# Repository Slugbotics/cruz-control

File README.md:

# f1tenth-2023

## CatCNN:
This requires miniconda for ease-of-use.
Note: Before running, change the `CatNN.yml` prefix field to match your conda environment location.
Follow this guide to copy the conda packages to your local environment: https://stackoverflow.com/questions/76864397/how-to-replicate-a-conda-environment#76867905

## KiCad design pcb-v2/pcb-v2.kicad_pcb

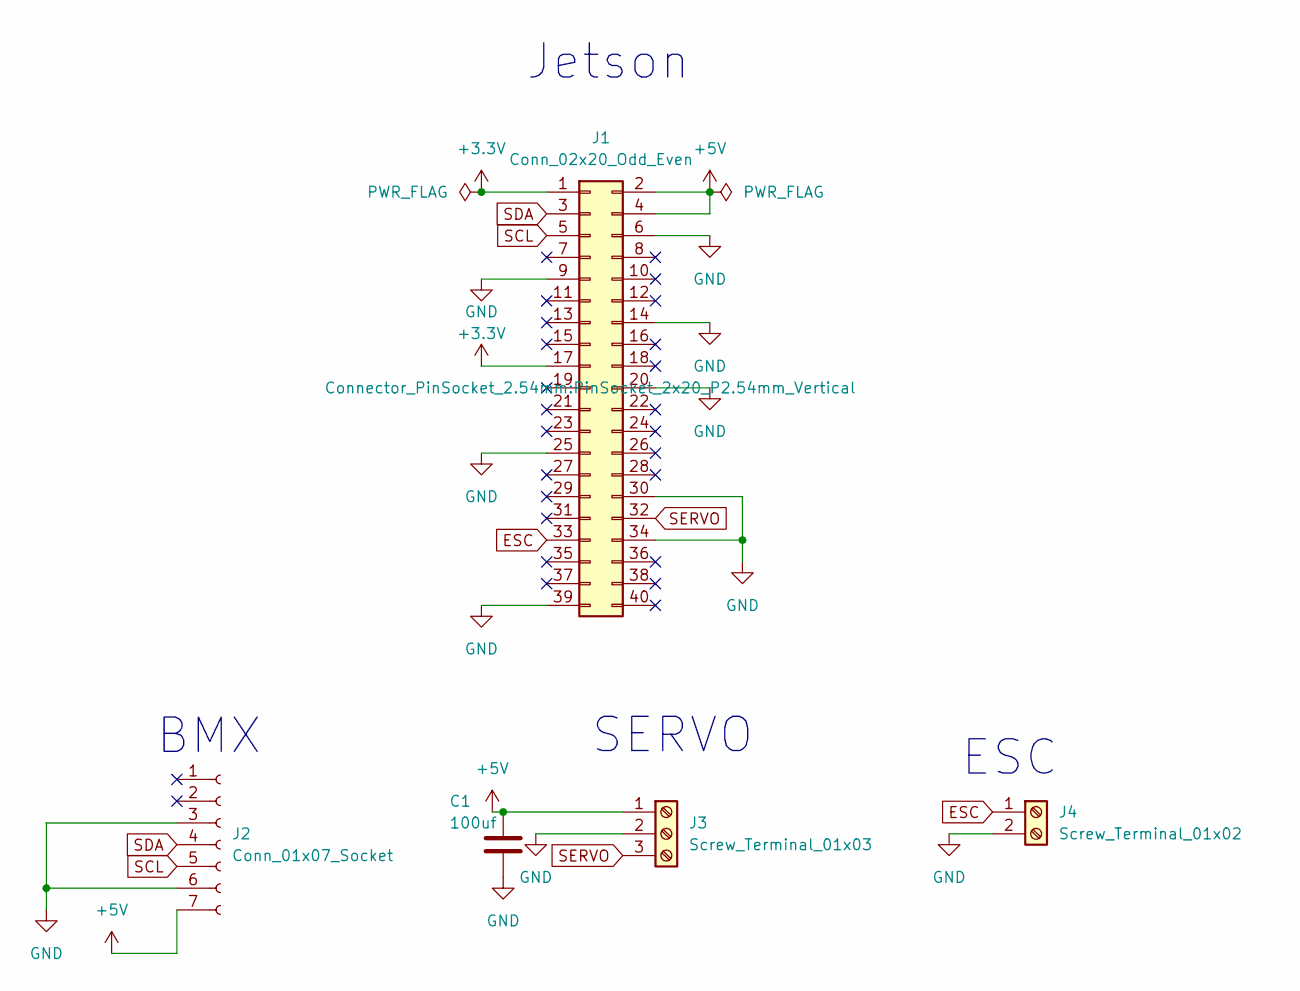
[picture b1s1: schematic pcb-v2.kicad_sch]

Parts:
C1: 100uf; CP_Radial_Tantal_D10.5mm_P5.00mm
J1: Conn_02x20_Odd_Even; PinSocket_2x20_P2.54mm_Vertical
J2: Conn_01x07_Socket; PinHeader_1x07_P2.54mm_Vertical
J3: Screw_Terminal_01x03; PinHeader_1x03_P2.54mm_Horizontal
J4: Screw_Terminal_01x02; PinHeader_1x02_P2.54mm_Horizontal

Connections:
+3.3V: J1.1, J1.17
+5V: C1.1, J1.2, J1.4, J2.7, J3.1
ESC: J1.33, J4.1
GND: C1.2, J1.6, J1.9, J1.14, J1.20, J1.25, J1.30, J1.34, J1.39, J2.3, J2.6, J3.2, J4.2
SCL: J1.5, J2.5
SDA: J1.3, J2.4
SERVO: J1.32, J3.3

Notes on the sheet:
BMX
SERVO
ESC
Jetson

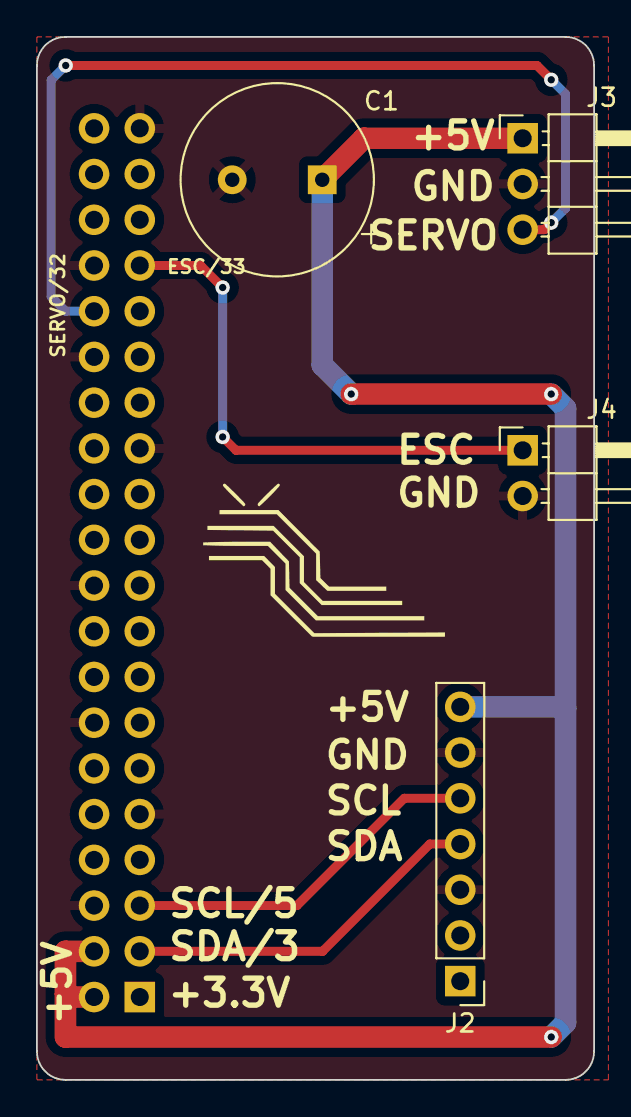
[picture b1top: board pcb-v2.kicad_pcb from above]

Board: 2 copper layers, 31.0 x 57.9 mm, 5 parts (1 on the bottom side), 7 nets.

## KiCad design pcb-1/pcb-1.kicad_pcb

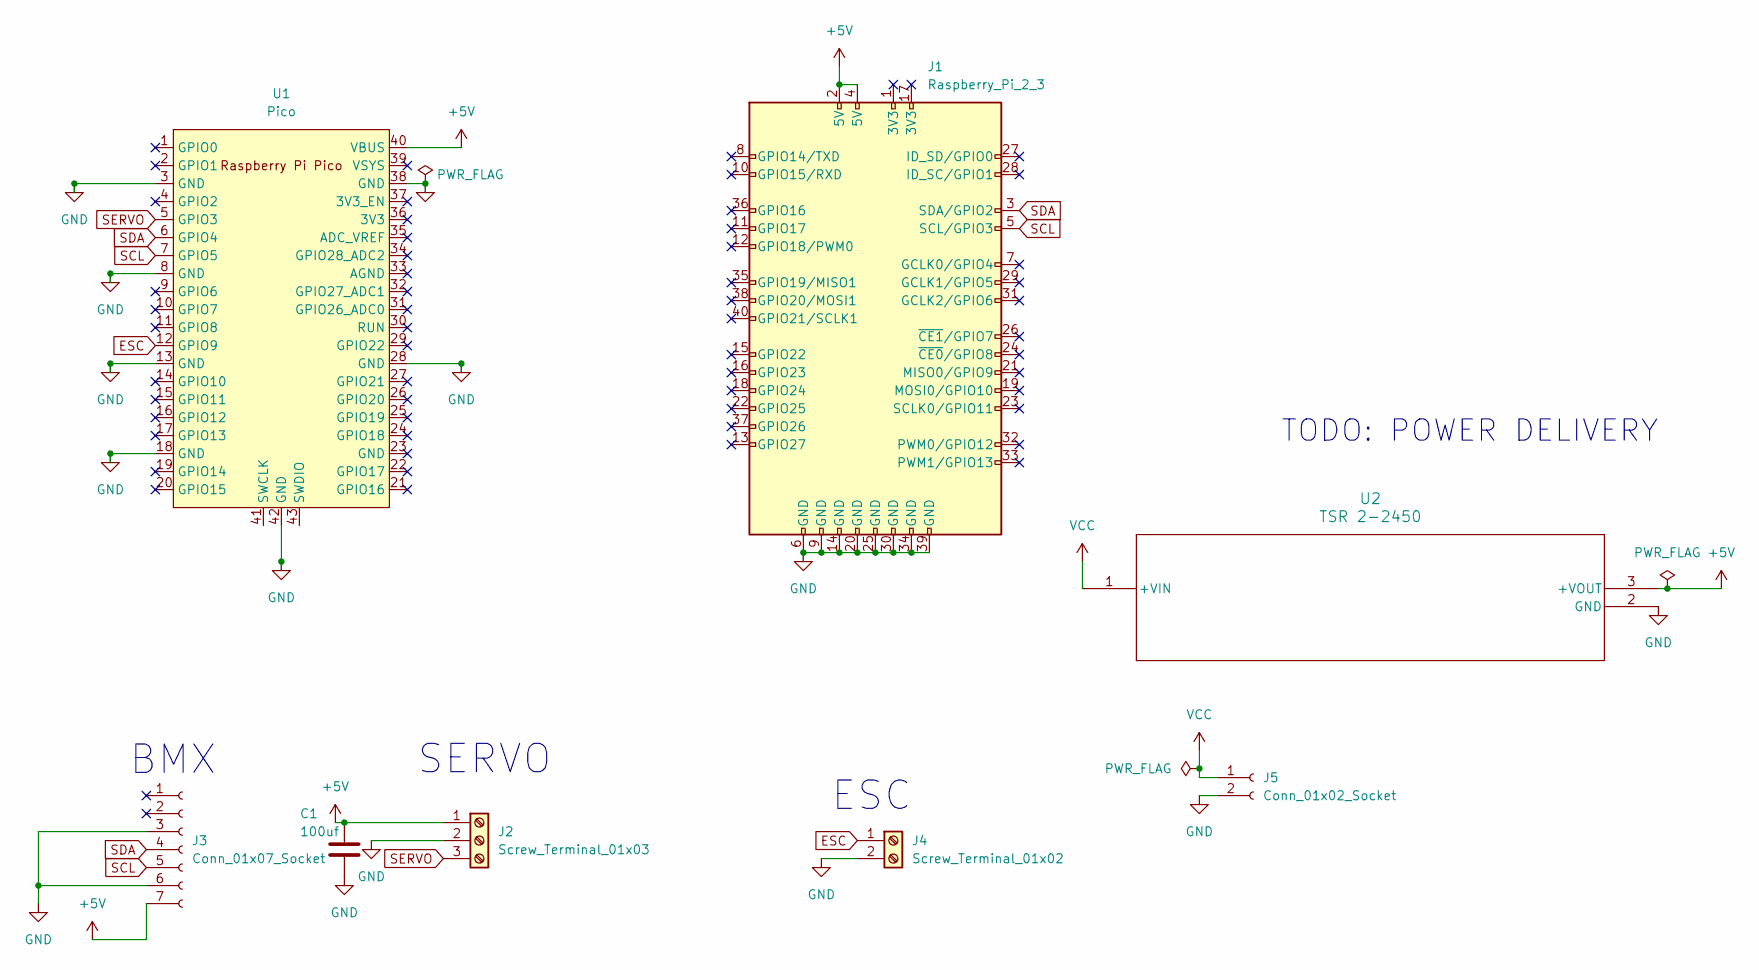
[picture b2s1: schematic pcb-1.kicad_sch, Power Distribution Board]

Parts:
C1: 100uf; CP_Radial_Tantal_D10.5mm_P5.00mm
J1: Raspberry_Pi_2_3; raspberrypi_2_3
J2: Screw_Terminal_01x03; CONN_1935174_PXC
J3: Conn_01x07_Socket; PinHeader_1x07_P2.54mm_Vertical
J4: Screw_Terminal_01x02; CONN2_710002_WRE
J5: Conn_01x02_Socket; AMASS_XT60-F_1x02_P7.20mm_Vertical
U1: Pico; RPi_Pico_SMD_TH
U2: TSR 2-2450; TSR 2-2450_TRP

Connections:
+5V: C1.1, J1.2 (5V), J1.4 (5V), J2.1, J3.7, U1.40 (VBUS), U2.3 (+VOUT)
ESC: J4.1, U1.12 (GPIO9)
GND: C1.2, J1.6 (GND), J1.9 (GND), J1.14 (GND), J1.20 (GND), J1.25 (GND), J1.30 (GND), J1.34 (GND), J1.39 (GND), J2.2, J3.3, J3.6, J4.2, J5.2, U1.3 (GND), U1.8 (GND), U1.13 (GND), U1.18 (GND), U1.28 (GND), U1.38 (GND), U1.42 (GND), U2.2 (GND)
SCL: J1.5 (SCL/GPIO3), J3.5, U1.7 (GPIO5)
SDA: J1.3 (SDA/GPIO2), J3.4, U1.6 (GPIO4)
SERVO: J2.3, U1.5 (GPIO3)
VCC: J5.1, U2.1 (+VIN)

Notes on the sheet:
TODO: POWER DELIVERY
BMX
ESC
SERVO

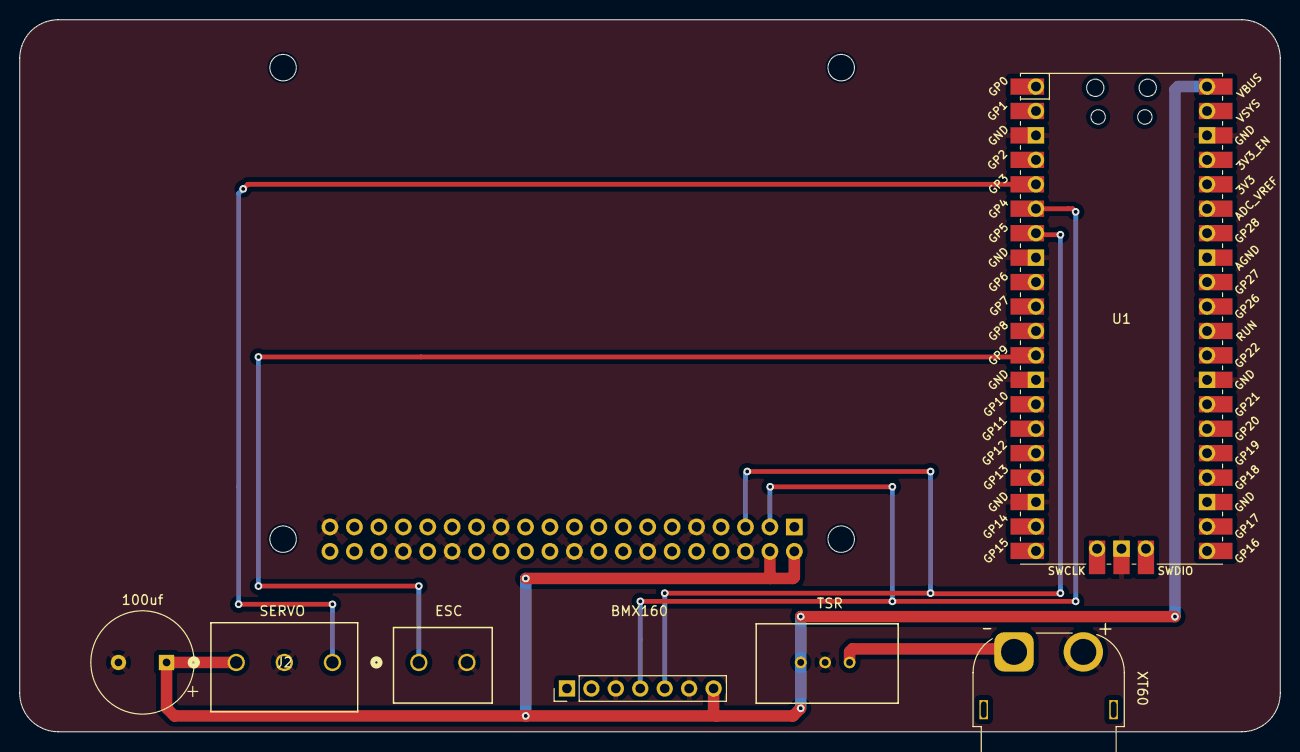
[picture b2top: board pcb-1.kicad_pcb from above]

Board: 2 copper layers, 131.0 x 74.0 mm, 9 parts (0 on the bottom side), 7 nets.

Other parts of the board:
BMX160-Drawing: LOGO

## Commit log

2023-11-22 time-to-collision braking
    Added lab2 automatic braking, read readme
2023-12-01 Added to readme, added lab3ws
2023-12-01 undid changes to main lab3branch
2023-12-01 undid commit to lab2
2023-12-03 added lab2_ws
    added lab2_ws
2024-01-17 Tested arduino servo library
    plan to have -90 to 90 sent from Raspberry Pi, arduino reads from 0 to 180 with 90 being center. use i2c comm with arduino being slave
2024-01-22 picoi2ccms
    added pico i2c comm file
2024-01-23 Added PCB files and Pico code
2024-01-24 Fixed i2c communication & implemented imu for pico
2024-01-24 modified: Pico/Pico.ino
2024-01-24 added camera files to git
2024-01-24 testing files
2024-01-24 finished i2c communication
2024-01-24 servo and esc communication
2024-01-25 Test
2024-01-25 ESC Test
2024-01-25 i2c communication updates
2024-01-26 Updated pico code
    mapped input to value ranges
2024-01-29 intial pcb push
2024-01-29 updated directory naming, completed routing? (still unsure about decoupling cap location)
2024-01-29 pcb rerouted with updated trace widths/dimensions
2024-01-29 removed bad 3v3 net, adjusted dimensions
2024-01-29 flipped pi - consider rerouting bmx160 so it isn't hanging off the board?
2024-01-29 moved trace down a little to avoid thermal relief warning
2024-01-29 added gitignore
2024-01-30 added camera test
2024-01-30 Added code for camera test
2024-01-30 updates to pcb
2024-01-30 deleted lockfile
2024-01-30 refill zones
2024-01-31 added gerber files
2024-02-01 Initial upload of convolutional neural network
2024-02-02 update documentation
2024-02-02 Add package list and retrained model
2024-02-02 push
2024-02-03 Lane Following V1
2024-02-06 Added code to spawn ego vehicle in carla script, must add control features from the lane follow model
2024-02-08 Controller worky
2024-02-08 lane_follow/lane_following.py
2024-02-08 added master.py
2024-02-09 Controller wireless working
2024-02-09 Added code to carla simulation script, but still need to work on image generation/processing
2024-02-10 added bluetooth controller support
    btc support bluetooth controllers, use instead of master.py
2024-02-12 modified: .gitignore modified: Pi/btc.py new file: VisionML/dk_loader.py new file: VisionML/eval.py new file: VisionML/model.py new file: VisionML/model2.py new file: VisionML/train.py new file: Visi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
2024-02-12 removed softmax from model output
2024-02-12 Added title to board
2024-02-13 test commit bluetooth controller
2024-02-13 fixed/cleaned btc.py
    fixed order, added named variables, cleaned up general bugs
2024-02-14 Working bluetooth code
2024-02-14 Merged code to master.py, File name changes
    Renamed files, combined bluetooth controller code together and sensor code to record into csv file
    Added comments to main
    Renamed files
2024-02-14 Working
2024-02-14 added csvfield parameter to csvwriter
    would not compile without having the fieldname parameter
2024-02-14 bugfixes
2024-02-14 modified: VisionML/dk_loader.py modified: VisionML/eval.py modified: VisionML/model2.py modified: VisionML/train2.py
2024-02-15 modified: bluetooth_control.py new file: bt_all.py modified: master.py
2024-02-15 Added
2024-02-15 Adjusted code to generate environment from camera POV, model code is commented out at the moment
2024-02-15 Removed vehicle randomness
2024-02-16 Center Servo
2024-02-16 Added pi code
2024-02-16 Cooked
2024-02-16 Adjusted camera location and car type
2024-02-17 Ignore .avi
2024-02-17 Camera input is working but ValueError occurs when passing input to model
2024-02-18 Added comments and dely to pico code
2024-02-19 cleanup variable names, assignment
    small cleanup to variable names
    (target -> throttle)
    changed how logic was done to determine sign integer
2024-02-19 changed directory saving for train2.py
2024-02-20 Model input is now working
2024-02-20 modified: master.py
2024-02-20 update slave address
2024-02-21 Added Pi control of servos in bluetooth_test.py
    added servo library, clean up code, add comments
2024-02-21 removed extra bluetooth files
2024-02-21 fixed XB_AXIS_MAP
    enum can now be read immediately as .value instead of an enum object with a value and name, use like c++ enums now
2024-02-21 mapping change on steer to percent
    change from angle to percent, as the servo already gives its max range as -1, 1
2024-02-22 init pcb-v2
2024-02-22 pcb-v2 r1
2024-02-22 pcb-v2 r2
2024-02-22 pcb-v2 rc1
2024-02-22 yeah
2024-02-22 Adjusted camera height
2024-02-22 more pcb-v2 stuff
2024-02-23 Added servo test code
2024-02-23 raw file to csv
2024-02-23 Update Makefile
2024-02-23 updated makefile
2024-02-27 updated silkscreen
2024-02-29 add test jetson files
2024-03-01 modified: bluetooth_test.py
2024-03-01 update camera input reading
2024-03-03 added datacollection file, reorganized repo
    changed camera class to be a helper function for data collection
    added datacollection to collect data
2024-03-04 cleaned pi repo, tested data-collection code
    deleted microsoft.gpg, slugbot-stream (camera test), wired-controller (using bluetooth only), pi-only (pi esc&servo control test)
    tested data-collection code
    renamed camera -> CAMERA (all components have all caps naming)
    renamed csv_out -> data_out (all data is dumped into one file, not just csv)
2024-03-04 added hokyuo collection
    cleaned up data_collection, all components are initialized using class and record data using some .record() function
    moved initialization and recording functions to class in each component file
    deleted old folders (pico related folders)
2024-03-04 added nuscenes tutorials
2024-03-05 Managed to sync can with scene
2024-03-06 got image and converted to tensor
2024-03-07 Nuscenes kinda working
2024-03-07 Fixed nuscenes bugs
2024-03-08 deleted: jetson/bluetooth_test.py deleted: jetson/camera.py jetson/BluetoothControl.py jetson/CAMERA.py jetson/HOKUYOLX.py jetson/WireControl.py jetson/data_collection.py jetson/pwm.py
2024-03-08 thingy thing
2024-03-09 Added nuscenes stuff
2024-03-09 Updated scripts
2024-03-10 Updated earrer
2024-03-11 Update bearer
2024-03-11 nuscenes py file
2024-03-11 run.py ready
2024-03-11 New Bearere
2024-03-11 It's jover
2024-03-12 updated yaml files
2024-03-12 Added zip for nuscenes download
2024-03-12 import
2024-03-12 Added dependencies for the nuscenes
2024-03-12 Updated pod request sizes
2024-03-12 Made changes to the run script and moved the nautilis scrips
2024-03-13 Changed path
2024-03-13 Fixed bugs
2024-03-13 Changed to CUDA
2024-03-13 Printing
2024-03-15 Organized code
2024-03-15 Changed git ignore
2024-03-15 Run.py changes
2024-03-15 cuda
2024-03-15 Stopped experimenting with cephfs-block
2024-03-15 Rename README to README.md
2024-03-15 better device selection
2024-03-15 Removed print
2024-03-16 desktop files
2024-03-17 Better debugging
2024-03-17 Changes to scripts
2024-03-17 Updated for version 1.1 of pth model
2024-03-17 Added code to print the model output
2024-03-17 Added visualization in notebook
2024-03-17 Added more visualization in notebook
2024-03-18 Whack
2024-03-18 Lots of changes
2024-03-18 Added lane_following_v2
2024-03-18 Updated run script
2024-03-18 Messed with batch size and epochs
2024-03-23 Cooking
2024-03-25 Model testing for rl camera.
2024-03-25 Add waymo dataset scripts
2024-03-26 Gazebo
2024-03-26 More Documentation
2024-03-27 Add download script
2024-03-27 udpated file paths
2024-03-27 Updated waymo pod
2024-03-27 modified download script
2024-03-27 updated portion files
2024-03-27 testing
2024-03-27 Modified portioning
2024-03-30 Updated download script
2024-03-30 Add perception pod
2024-04-04 Nuscense 1.2 training updated to tensor use
2024-04-05 Running desktop stream
2024-04-05 updated claim script
2024-04-06 Updated desktop to work with seaweed
2024-04-08 Created Nautilus UI Guide
2024-04-08 Added some context and fixed grammatical issues
